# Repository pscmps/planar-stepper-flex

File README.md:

# Planar Stepper Flex

プリント配線をモータ巻線として使うXY平面ステッパの試作一式です。Pico 2 W、秋月電子の`AE-DRV8835-S` 4個、2種類の2層FPCを対象にしています。

> 現在は非公開で検証中です。回路・FPC・ファームウェアはいずれも試作品で、連続電流定格を保証していません。

## 収録内容

| ディレクトリ | 内容 |
|---|---|
| `hardware/pico2w-drv8835-controller/` | Pico 2 WとDRV8835 4個を載せる制御基板 |
| `hardware/drv8835-driver-module/` | 外部マイコン用DRV8835 4個基板 |
| `hardware/flex-50mm/` | 有効配線領域50 x 50 mmのFPC |
| `hardware/flex-4cards/` | 名刺4枚相当の有効配線領域を持つFPC。手描きシルク入り |
| `firmware/pico2-drv8835/` | USB G-code版、診断版、Pico 2 W Wi-Fi版 |
| `generator/` | 寸法指定可能なFPC生成器と手描きシルク注入処理 |
| `manufacturing/v0.1.0/` | DRC確認済みGerber ZIP、BOM、表裏PNG、ハッシュ |

## 基板プレビュー

| Pico 2 W制御基板 | DRV8835単独基板 |
|---|---|
|  |  |

| 50 mm FPC | 名刺4枚サイズFPC |
|---|---|
|  |  |

背面画像は各`manufacturing/v0.1.0/<board>/back.png`にあります。

## 最短手順

1. [安全上の注意](docs/safety.md)と[配線表](docs/wiring.md)を確認します。
2. VMを切った状態でPicoを起動し、DRV8835入力がLowであることを確認します。
3. 外付け直列抵抗と安定化電源の電流制限を使い、低い電圧・短い励磁から試します。
4. ファームウェアは[ビルド手順](docs/firmware-build.md)に従って生成します。
5. 基板を変更した場合は[製造データ手順](docs/manufacturing.md)でDRCとZIPを再生成します。

FPC生成器の使い方は[基板生成](docs/board-generation.md)、設計元と参考資料は[参考資料](docs/references.md)を参照してください。

## ライセンス

このリポジトリは複数ライセンスです。

| 対象 | ライセンス |
|---|---|
| ハードウェア設計、FPC、KiCadデータ、Gerberなど | [CERN-OHL-P-2.0](LICENSES/CERN-OHL-P-2.0.txt) |
| ファームウェア、生成器、プロジェクト独自ソフトウェア | [MIT](LICENSES/MIT.txt) |
| README、文書、プロジェクト独自の説明画像 | [CC BY 4.0](LICENSES/CC-BY-4.0.txt) |

第三者由来のコード、フットプリント、ライブラリには元のライセンスが適用されます。適用範囲と例外は[ライセンスと権利](RIGHTS.md)、第三者依存は[第三者通知](THIRD_PARTY_NOTICES.md)を参照してください。

## 使用報告は任意です

この設計を使って何か作った場合、作品や写真を教えていただけると嬉しいです。使用報告や連絡は必須ではありません。

If you build, modify, or incorporate this design into a project, the author would be happy to hear about it and see photos of your work. Reporting your use or contacting the author is entirely optional.

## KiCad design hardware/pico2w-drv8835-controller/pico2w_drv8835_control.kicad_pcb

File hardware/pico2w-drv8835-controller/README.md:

# Pico 2 W + AE-DRV8835-S制御基板

Pico 2 Wと`AE-DRV8835-S` 4個を載せ、A/B/C/D相を個別駆動する2層基板です。

- 外形: 80 x 85 mm、角R5 mm
- 相配線: 1.5 mm
- VM配線: 2.0 mm、X/Y別系統
- モジュール: 2.54 mm、列間7.62 mm、1相につき1個
- X出力: `A+ / A- / B+ / B-`
- Y出力: `C+ / C- / D+ / D-`

GPIO、AS5600、サーボ、将来microSDの割当は[`../../docs/wiring.md`](../../docs/wiring.md)を参照してください。VM_X/VM_Yを共通化する場合は両方のVMはんだジャンパを閉じ、電源入力は片側だけを使います。

製造ZIP、BOM、DRCレポートは[`../../manufacturing/v0.1.0/pico2w-drv8835-controller/`](../../manufacturing/v0.1.0/pico2w-drv8835-controller/)にあります。

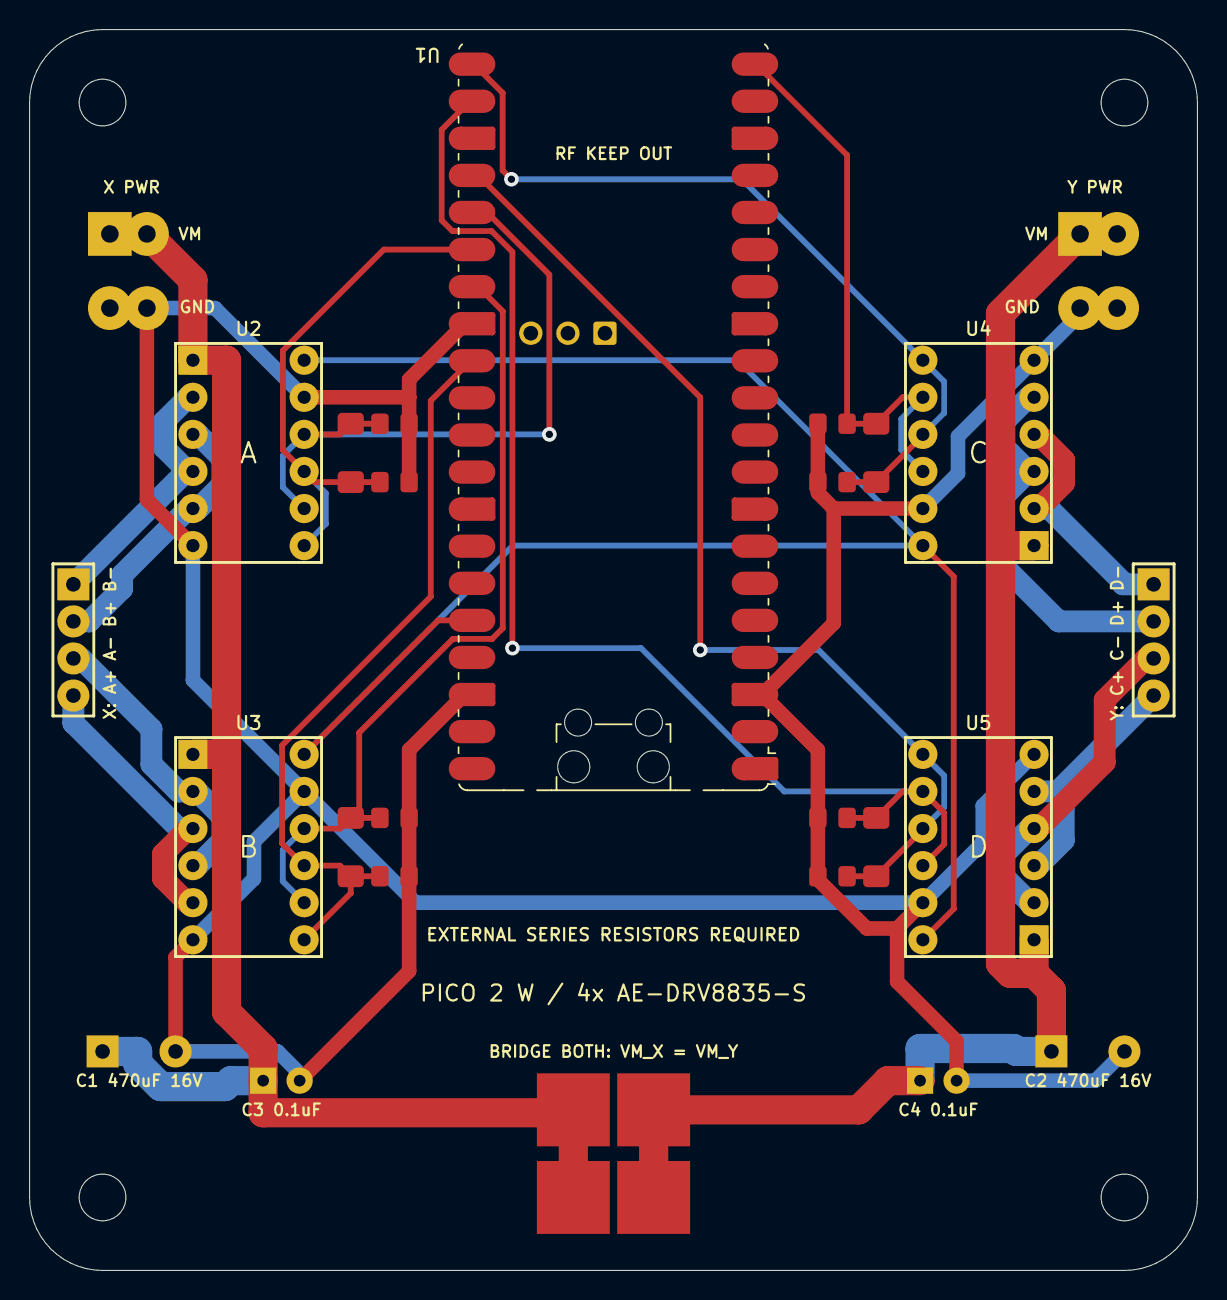
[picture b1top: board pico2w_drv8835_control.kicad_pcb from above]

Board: 2 copper layers, 80.0 x 85.0 mm, 35 parts (0 on the bottom side), 20 nets.

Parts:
C1, C2: 470uF 16V
C3, C4: 0.1uF
H1, H2, H3, H4: MountingHole_3.2mm
J1: X POWER SPLIT 2x2
J2: Y POWER SPLIT 2x2
J3: X OUTPUT
J4: Y OUTPUT
R1, R2, R3, R4, R5, R6, R7, R8: 10k PULLDOWN
SJ1, SJ2: VM_X-VM_Y LINK
TP1: A_IN1
TP2: A_IN2
TP3: B_IN1
TP4: B_IN2
TP5: C_IN1
TP6: C_IN2
TP7: D_IN1
TP8: D_IN2
U1: Raspberry Pi Pico 2 W; RaspberryPi_Pico_W_SMD_HandSolder
U2: AE-DRV8835-S PHASE A
U3: AE-DRV8835-S PHASE B
U4: AE-DRV8835-S PHASE C
U5: AE-DRV8835-S PHASE D

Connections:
+3V3: U1.36, U2.12, U3.12, U4.12, U5.12
A+: J3.1, U2.2, U2.4
A-: J3.2, U2.3, U2.5
A_IN1: R1.1, TP1.1, U1.25, U2.8, U2.10
A_IN2: R2.1, TP2.1, U1.26, U2.7, U2.9
B+: J3.3, U3.2, U3.4
B-: J3.4, U3.3, U3.5
B_IN1: R3.1, TP3.1, U1.27, U3.8, U3.10
B_IN2: R4.1, TP4.1, U1.29, U3.7, U3.9
C+: J4.1, U4.2, U4.4
C-: J4.2, U4.3, U4.5
C_IN1: R5.1, TP5.1, U1.20, U4.8, U4.10
C_IN2: R6.1, TP6.1, U1.21, U4.7, U4.9
D+: J4.3, U5.2, U5.4
D-: J4.4, U5.3, U5.5
D_IN1: R7.1, TP7.1, U1.22, U5.8, U5.10
D_IN2: R8.1, TP8.1, U1.24, U5.7, U5.9
GND: C1.2, C2.2, C3.2, C4.2, J1.3, J1.4, J2.3, J2.4, R1.2, R2.2, R3.2, R4.2, R5.2, R6.2, R7.2, R8.2, U1.3, U1.28, U1.38, U2.6, U2.11, U3.6, U3.11, U4.6, U4.11, U5.6, U5.11
VM_X: C1.1, C3.1, J1.1, J1.2, SJ1.1, SJ2.1, U2.1, U3.1
VM_Y: C2.1, C4.1, J2.1, J2.2, SJ1.2, SJ2.2, U4.1, U5.1

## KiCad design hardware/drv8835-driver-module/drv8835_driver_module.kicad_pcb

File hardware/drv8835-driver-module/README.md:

# AE-DRV8835-S単独ドライバ基板

外部マイコンからA/B/C/D相を制御する、`AE-DRV8835-S` 4個の2層基板です。

- 外形: 48 x 60 mm、角R3 mm
- 入力J1: 上段X=`VCC GND A1 A2 B1 B2`、下段Y=`VCC GND C1 C2 D1 D2`
- X出力J4: `A+ / A- / B+ / B-`
- Y出力J5: `C+ / C- / D+ / D-`
- 固定穴: φ3.2 mm NPTH 4個

入力`A1/A2`などはモータ出力名ではなく、対応する相モジュールの`IN1/IN2`です。各入力には10 kohmプルダウンがあります。VM_X/VM_Yは通常分離し、共通化する場合はVMはんだジャンパを両方閉じます。

製造ZIP、BOM、DRCレポートは[`../../manufacturing/v0.1.0/drv8835-driver-module/`](../../manufacturing/v0.1.0/drv8835-driver-module/)にあります。

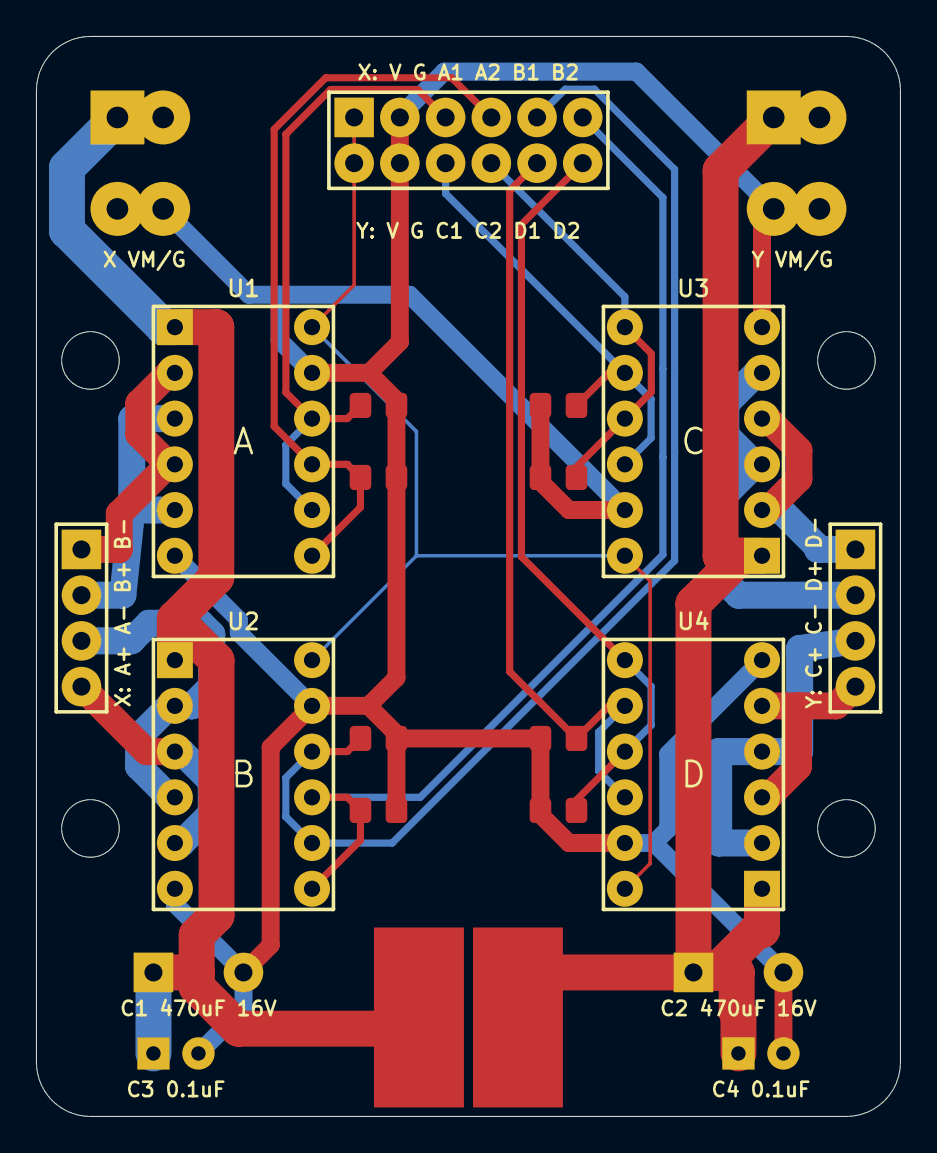
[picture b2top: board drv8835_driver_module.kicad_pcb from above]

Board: 2 copper layers, 48.0 x 60.0 mm, 27 parts (0 on the bottom side), 20 nets.

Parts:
C1, C2: 470uF 16V
C3, C4: 0.1uF
H1, H2, H3, H4: MountingHole_3.2mm
J1: MCU INPUT X/Y 2x6
J2: X POWER
J3: Y POWER
J4: X OUTPUT
J5: Y OUTPUT
R1, R2, R3, R4, R5, R6, R7, R8: 10k PULLDOWN
SJ1, SJ2: VM_X-VM_Y LINK
U1: AE-DRV8835-S PHASE A
U2: AE-DRV8835-S PHASE B
U3: AE-DRV8835-S PHASE C
U4: AE-DRV8835-S PHASE D

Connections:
A+: J4.1, U1.2, U1.4
A-: J4.2, U1.3, U1.5
A_IN1: J1.3, R1.1, U1.8, U1.10
A_IN2: J1.4, R2.1, U1.7, U1.9
B+: J4.3, U2.2, U2.4
B-: J4.4, U2.3, U2.5
B_IN1: J1.5, R3.1, U2.8, U2.10
B_IN2: J1.6, R4.1, U2.7, U2.9
C+: J5.1, U3.2, U3.4
C-: J5.2, U3.3, U3.5
C_IN1: J1.9, R5.1, U3.8, U3.10
C_IN2: J1.10, R6.1, U3.7, U3.9
D+: J5.3, U4.2, U4.4
D-: J5.4, U4.3, U4.5
D_IN1: J1.11, R7.1, U4.8, U4.10
D_IN2: J1.12, R8.1, U4.7, U4.9
GND: C1.2, C2.2, C3.2, C4.2, J1.2, J1.8, J2.3, J2.4, J3.3, J3.4, R1.2, R2.2, R3.2, R4.2, R5.2, R6.2, R7.2, R8.2, U1.6, U1.11, U2.6, U2.11, U3.6, U3.11, U4.6, U4.11
VCC: J1.1, J1.7, U1.12, U2.12, U3.12, U4.12
VM_X: C1.1, C3.1, J2.1, J2.2, SJ1.1, SJ2.1, U1.1, U2.1
VM_Y: C2.1, C4.1, J3.1, J3.2, SJ1.2, SJ2.2, U3.1, U4.1

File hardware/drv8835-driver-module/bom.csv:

参照,値,数量,備考
U1-U4,秋月電子 AE-DRV8835-S,4,各相に1モジュール・内部2ブリッジ並列
SOCKET-U1-U4,1x6 ピンソケット P2.54mm,8,モジュール1個につき2本
R1-R8,10k ohm 0805,8,入力プルダウン
C1-C2,470uF 16V ラジアル P5.00mm,2,極性注意
C3-C4,0.1uF セラミック P2.50mm,2,各軸VMバイパス
J1,2x6 ピンソケット P2.54mm,1,外部マイコン入力
J2-J3,1x2 ピンソケット P2.54mm,4,各軸のVM/GNDに2本ずつ・1接点3A以上
J4-J5,1x4 ピンソケット P2.54mm,2,モータ出力・1接点3A以上
SJ1-SJ2,半田ジャンパ,2,VM_X/VM_Y共通化時だけ両方を短絡
H1-H4,M3ねじ・スペーサー,4,基板穴径3.2mm・NPTH
EXT-R-A-D,1.5 ohm 5W 抵抗,4,初回電流制限用・基板外へ直列接続

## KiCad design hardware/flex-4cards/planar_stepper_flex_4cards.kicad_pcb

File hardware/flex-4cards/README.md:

# 名刺4枚サイズXY平面ステッパーFPC

標準名刺91 x 55 mmを2 x 2で並べた範囲を有効配線領域とする大型2層FPCです。

- 外形: 229.0 x 156.5 mm
- 有効配線領域: 182.5 x 110.0 mm
- ピッチ: 5.0 mm
- B/D相オフセット: 2.5 mm
- 配線幅: 1.8 mm
- 補助SMD端子: 表裏に各4極、既存PTH列から長手方向へ10 mm離して配置
- 手描きシルク: 生成時に`generator/assets/hand-drawn-silkscreen.kicad_mod`から追加

概算配線長と抵抗はA=4967.5 mm/1.359 ohm、B=4665.1 mm/1.277 ohm、C=4887.5 mm/1.337 ohm、D=4577.6 mm/1.253 ohmです。銅厚35 um、銅抵抗率1.724e-8 ohm mによる一次概算です。

このPCBは直接編集せず、[`../../docs/board-generation.md`](../../docs/board-generation.md)の`--preset 4cards --with-art`で再生成します。製造ZIPは[`../../manufacturing/v0.1.0/flex-4cards/`](../../manufacturing/v0.1.0/flex-4cards/)にあります。

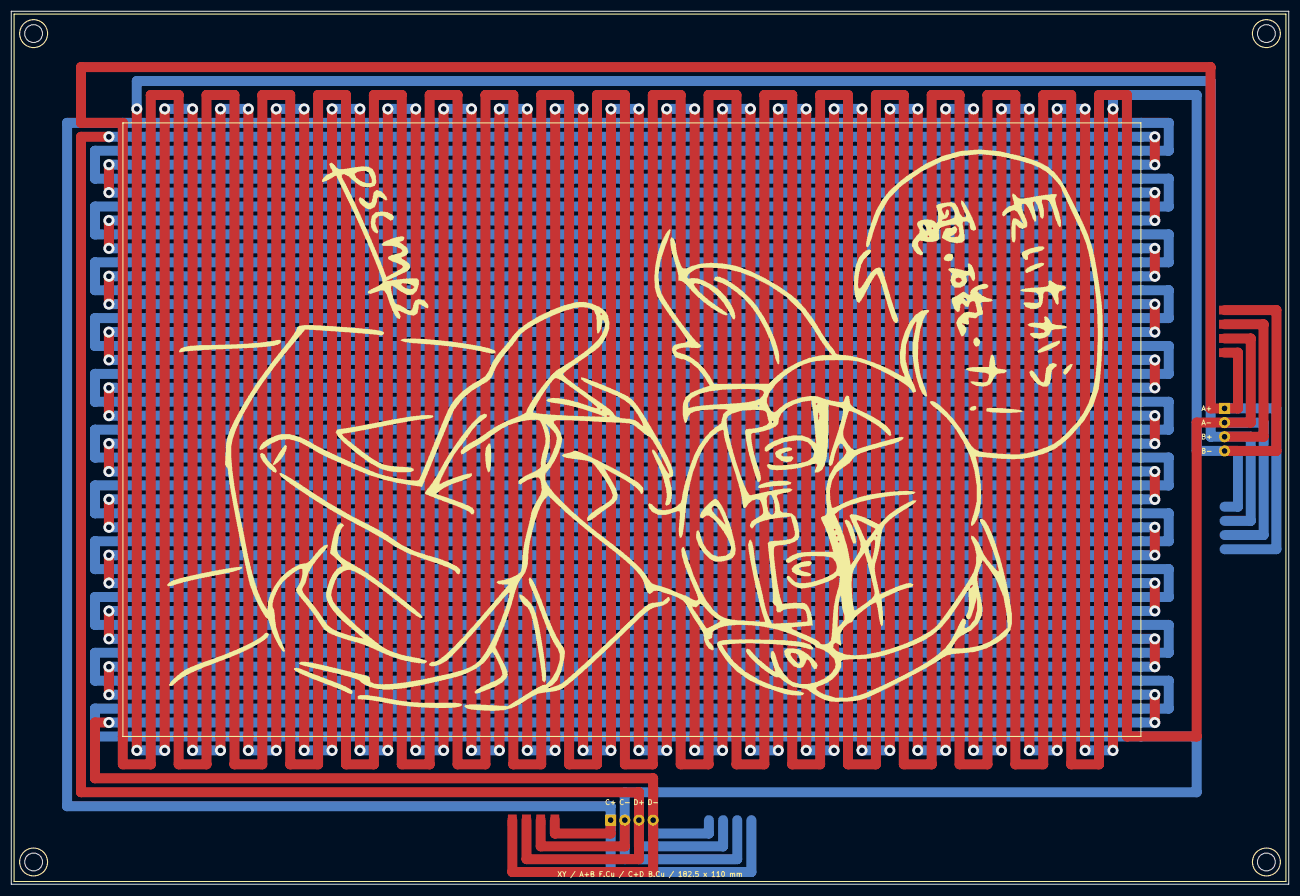
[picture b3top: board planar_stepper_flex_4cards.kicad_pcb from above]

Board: 2 copper layers, 229.0 x 156.5 mm, 6 parts (0 on the bottom side), 4 nets.

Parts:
H1, H2, H3, H4: MountingHole_3.2mm
J1, J2: Conn_01x04_Pin_2.54mm

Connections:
COIL_A: J1.1, J1.2
COIL_B: J1.3, J1.4
COIL_C: J2.1, J2.2
COIL_D: J2.3, J2.4

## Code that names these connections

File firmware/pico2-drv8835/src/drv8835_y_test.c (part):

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#define FW_NAME "pico2-gcode-drv8835-xy-test"
#define FW_VERSION "0.4.0"

#define PIN_C_IN1 15u
#define PIN_C_IN2 16u
#define PIN_D_IN1 17u
#define PIN_D_IN2 18u
#define PIN_A_IN1 19u
#define PIN_A_IN2 20u
#define PIN_B_IN1 21u
#define PIN_B_IN2 22u

#define PWM_FREQUENCY_HZ 20000u
#define PWM_COUNTER_HZ 10000000u
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};

static const unsigned int phase_pins[2][4] = {
    {PIN_A_IN1, PIN_B_IN2, PIN_A_IN2, PIN_B_IN1},
    {PIN_C_IN1, PIN_D_IN2, PIN_C_IN2, PIN_D_IN1},
};

static const unsigned int driver_pins[8] = {
    PIN_A_IN1, PIN_A_IN2, PIN_B_IN1, PIN_B_IN2,
    PIN_C_IN1, PIN_C_IN2, PIN_D_IN1, PIN_D_IN2,
};

static const char *axis_names[2] = {"X", "Y"};
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};

static const unsigned int coil_positive_pins[2][2] = {
    {PIN_A_IN1, PIN_B_IN1},
    {PIN_C_IN1, PIN_D_IN1},
};

static const unsigned int coil_negative_pins[2][2] = {
    {PIN_A_IN2, PIN_B_IN2},
    {PIN_C_IN2, PIN_D_IN2},
};

static void safe_gpio_init(void) {
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    if (strcmp(line, "M18") == 0 || strcmp(line, "M84") == 0) {
        all_off();
        printf("[MSG:DRV8835 XY outputs=HiZ X=GP%u/GP%u/GP%u/GP%u Y=GP%u/GP%u/GP%u/GP%u]\r\n",
               PIN_A_IN1, PIN_A_IN2, PIN_B_IN1, PIN_B_IN2, PIN_C_IN1,
               PIN_C_IN2, PIN_D_IN1, PIN_D_IN2);
        printf("ok\r\n");
        return;
    }
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    printf("[SAFE: DRV8835 IN/IN inputs initialized LOW; outputs HiZ]\r\n");
    printf("[PIN X: A AIN1=GP%u(physical25) AIN2=GP%u(physical26); "
           "B BIN1=GP%u(physical27) BIN2=GP%u(physical29)]\r\n",
           PIN_A_IN1, PIN_A_IN2, PIN_B_IN1, PIN_B_IN2);
    printf("[PIN Y: C AIN1=GP%u(physical20) AIN2=GP%u(physical21); "
           "D BIN1=GP%u(physical22) BIN2=GP%u(physical24); MODE=GND]\r\n",
           PIN_C_IN1, PIN_C_IN2, PIN_D_IN1, PIN_D_IN2);

    char line[128];
    size_t length = 0u;
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
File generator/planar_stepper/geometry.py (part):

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    ]
    pins = [*ab_pins, *cd_pins]

    a = PhaseGeometry(name="A", net_name="COIL_A", pin_names=("A+", "A-"))
    a.active_segments = _active_strokes(a_xs, motion_top, motion_bottom)
    a.return_segments = _returns(
        a_xs, motion_top, motion_bottom, config.return_offset_a, "F.Cu"
    )

    b = PhaseGeometry(name="B", net_name="COIL_B", pin_names=("B+", "B-"))
    b.active_segments = _active_strokes(b_xs, motion_top, motion_bottom)
    b.return_segments, b.via_points = _switched_vertical_returns(
        b_xs, motion_top, motion_bottom, config.switched_via_escape
    )

    c = PhaseGeometry(name="C", net_name="COIL_C", pin_names=("C+", "C-"))
    c.active_segments = _active_strokes_horizontal(c_ys, motion_left, motion_right)
    c.return_segments = _returns_horizontal(
        c_ys, motion_left, motion_right, config.return_offset_a, "B.Cu"
    )

    d = PhaseGeometry(name="D", net_name="COIL_D", pin_names=("D+", "D-"))
    d.active_segments = _active_strokes_horizontal(d_ys, motion_left, motion_right)
    d.return_segments, d.via_points = _switched_horizontal_returns(
        d_ys, motion_left, motion_right, config.switched_via_escape
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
